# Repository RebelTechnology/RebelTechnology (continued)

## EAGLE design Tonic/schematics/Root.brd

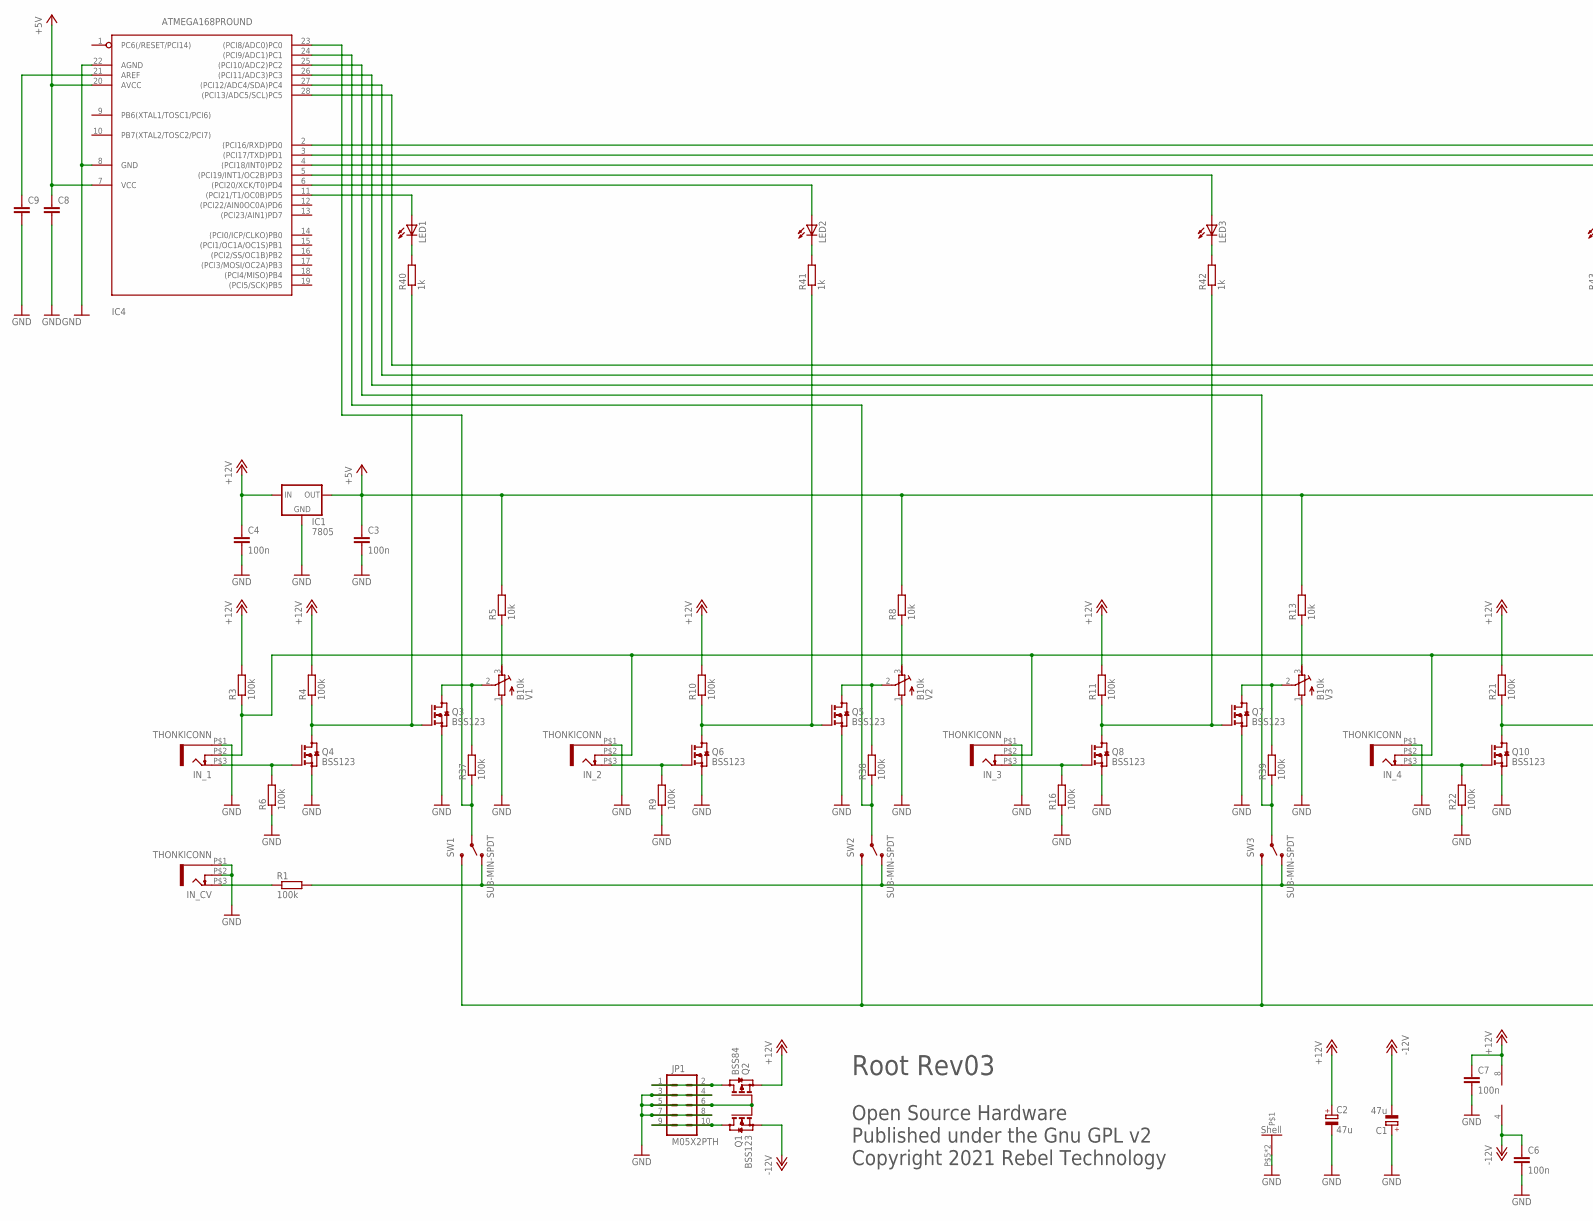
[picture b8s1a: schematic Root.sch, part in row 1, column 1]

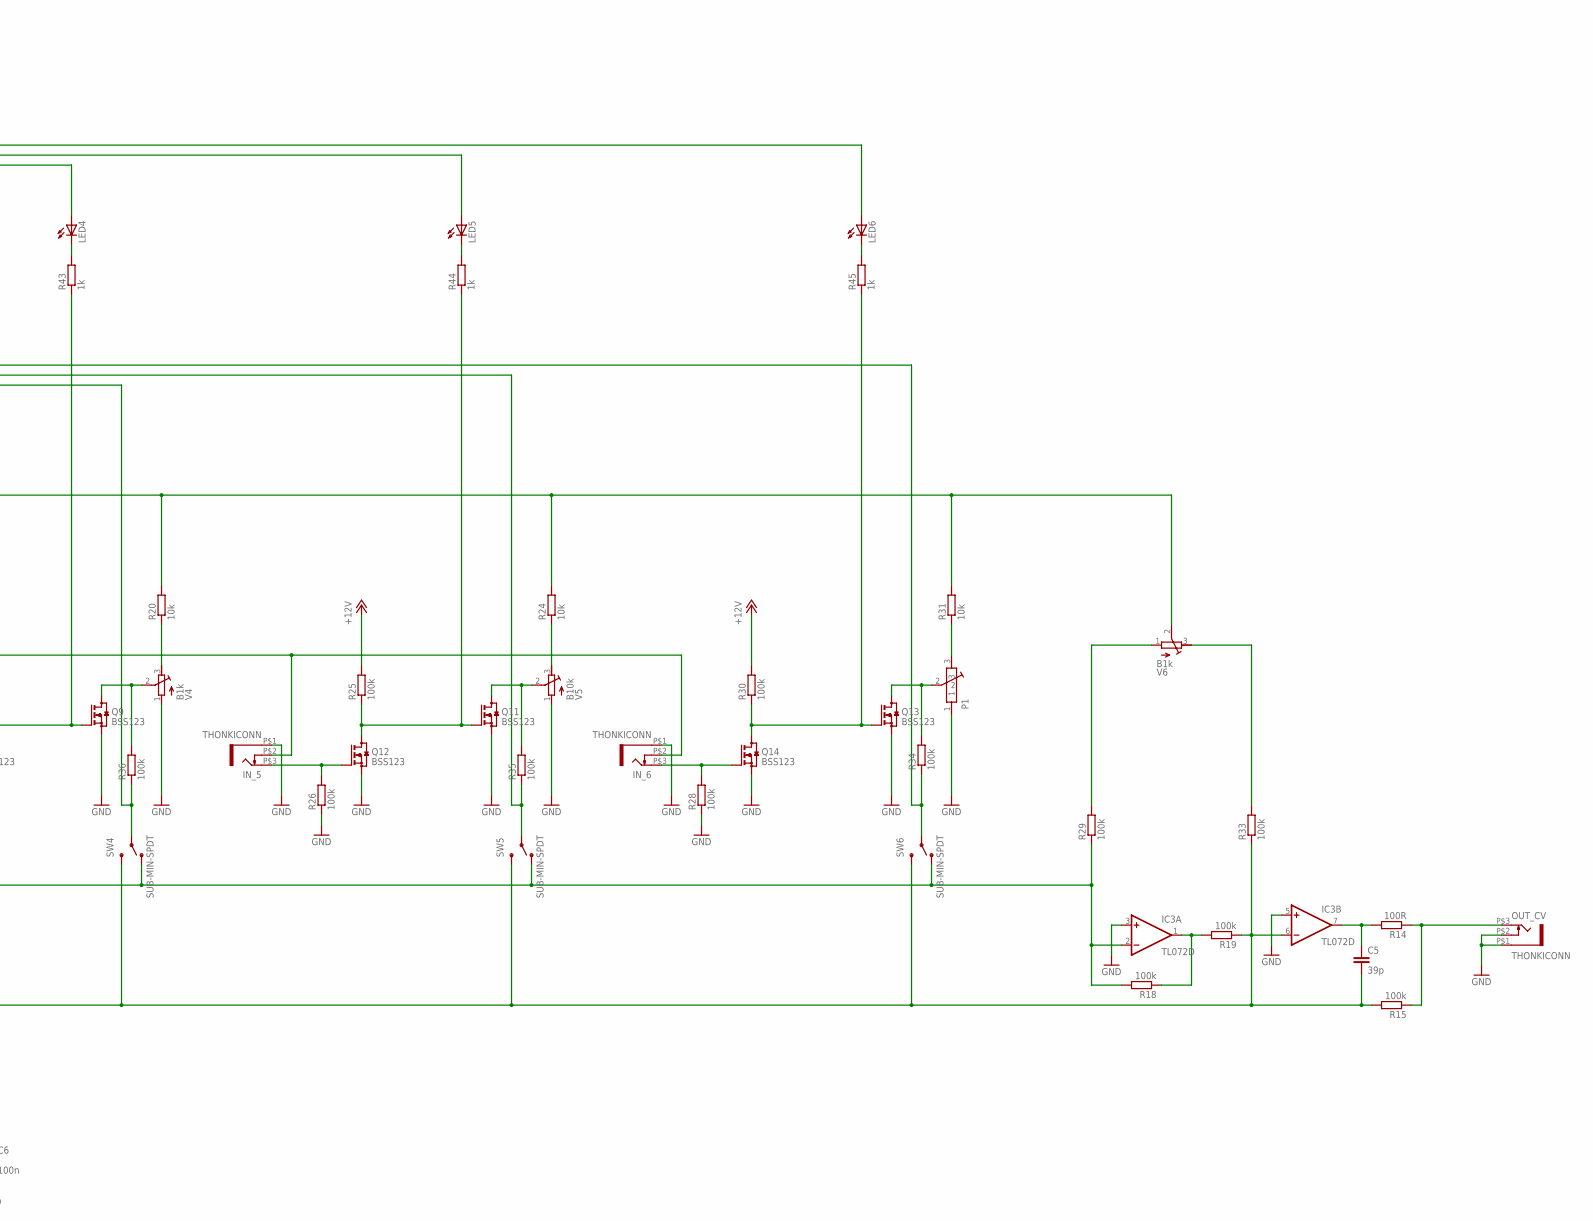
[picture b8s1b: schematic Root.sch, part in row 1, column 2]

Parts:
C1, C2: 47u; E5-6
C3, C4, C6, C7: 100n; C0603
C5: 39p; C0603
C8, C9: C-EUC0603; C0603
IC1: 7805; TO-92
IC3: TL072D; SO08
IC4: ATMEGA168PROUND; DIL28-3-ROUND
IN_1, IN_2, IN_3, IN_4, IN_5, IN_6: THONKICONN
IN_CV: THONKICONN
JP1: M05X2PTH; AVR_ICSP
LED1, LED2, LED3, LED4, LED5, LED6: LED3MM
OUT_CV: THONKICONN
P1: B1k; POT-ALPS-RK09L1140
Q1, Q3, Q4, Q5, Q6, Q7, Q8, Q9, Q10, Q11, Q12, Q13, Q14: BSS123; SOT23
Q2: BSS84; SOT23
R1, R3, R4, R6, R9, R10, R11, R15, R16, R18, R19, R21, R22, R25, R26, R28, R29, R30, R33, R34, R35, R36, R37, R38, R39: 100k; 0603
R5, R8, R13, R20, R24, R31: 10k; 0603
R14: 100R; 0603
R40, R41, R42, R43, R44, R45: 1k; 0603
SW1, SW2, SW3, SW4, SW5, SW6: SUB-MIN-SPDT
V1, V2, V3, V5: B10k; RTRIM3296W
V4, V6: B1k; RTRIM3296W

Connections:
+5V: C3.1, C8.1, IC1.3 (OUT), IC4.7 (VCC), IC4.20 (AVCC), R5.2, R8.2, R13.2, R20.2, R24.2, R31.2, V6.2 (S)
+12V: C2.+, C4.1, C7.1, IC1.2 (IN), IC3.8 (V+), Q2.2 (S), R3.2, R4.2, R10.2, R11.2, R21.2, R25.2, R30.2
-12V: C1.-, C6.1, IC3.4 (V-), Q1.2 (S)
GND: C1.+, C2.-, C3.2, C4.2, C6.2, C7.2, C8.2, C9.2, IC1.1 (GND), IC3.3 (+IN), IC3.5 (+IN), IC4.8 (GND), IC4.22 (AGND), IN_1.P$1 (5), IN_2.P$1 (5), IN_3.P$1 (5), IN_4.P$1 (5), IN_5.P$1 (5), IN_6.P$1 (5), IN_CV.P$1 (5), IN_CV.P$2 (4), JP1.3, JP1.4, JP1.5, JP1.6, JP1.7, JP1.8, OUT_CV.P$1 (5), OUT_CV.P$2 (4), P1.1, P1.P$5, P1.P$6, Q1.1 (G), Q2.1 (G), Q3.2 (S), Q4.2 (S), Q5.2 (S), Q6.2 (S), Q7.2 (S), Q8.2 (S), Q9.2 (S), Q10.2 (S), Q11.2 (S), Q12.2 (S), Q13.2 (S), Q14.2 (S), R6.1, R9.1, R16.1, R22.1, R26.1, R28.1, V1.1 (A), V2.1 (A), V3.1 (A), V4.1 (A), V5.1 (A)
unnamed: Q3.3 (D), R37.2, V1.2 (S)
unnamed: OUT_CV.P$3 (3), R14.1, R15.1
unnamed: IN_1.P$3 (3), Q4.1 (G), R6.2
unnamed: JP1.9, JP1.10, Q1.3 (D)
unnamed: R8.1, V2.3 (E)
unnamed: C9.1, IC4.21 (AREF)
unnamed: IC4.23 ((PCI8/ADC0)PC0), R37.1, SW1.2
unnamed: Q5.3 (D), R38.2, V2.2 (S)
unnamed: Q7.3 (D), R39.2, V3.2 (S)
unnamed: Q9.3 (D), R36.2, V4.2 (S)
unnamed: P1.2, Q13.3 (D), R34.2
unnamed: Q11.3 (D), R35.2, V5.2 (S)
unnamed: IN_2.P$3 (3), Q6.1 (G), R9.2
unnamed: IN_1.P$2 (4), IN_2.P$2 (4), IN_3.P$2 (4), IN_4.P$2 (4), IN_5.P$2 (4), IN_6.P$2 (4), R3.1
unnamed: Q5.1 (G), Q6.3 (D), R10.1, R41.1
unnamed: IC4.24 ((PCI9/ADC1)PC1), R38.1, SW2.2
unnamed: IN_CV.P$3 (3), R1.1
unnamed: P1.3, R31.1
unnamed: R13.1, V3.3 (E)
unnamed: Q3.1 (G), Q4.3 (D), R4.1, R40.1
unnamed: IN_3.P$3 (3), Q8.1 (G), R16.2
unnamed: Q7.1 (G), Q8.3 (D), R11.1, R42.1
unnamed: R29.2, V6.1 (A)
unnamed: IC4.25 ((PCI10/ADC2)PC2), R39.1, SW3.2
unnamed: IC4.28 ((PCI13/ADC5/SCL)PC5), R34.1, SW6.2
unnamed: R20.1, V4.3 (E)
unnamed: C5.1, IC3.7 (OUT), R14.2
unnamed: IN_4.P$3 (3), Q10.1 (G), R22.2
unnamed: IC3.1 (OUT), R18.1, R19.2
unnamed: LED3.K (C), R42.2
unnamed: Q9.1 (G), Q10.3 (D), R21.1, R43.1
unnamed: R33.2, V6.3 (E)
unnamed: IC4.26 ((PCI11/ADC3)PC3), R36.1, SW4.2
unnamed: LED4.K (C), R43.2
unnamed: LED5.K (C), R44.2
unnamed: LED6.K (C), R45.2
unnamed: R24.1, V5.3 (E)
unnamed: R5.1, V1.3 (E)
unnamed: IN_5.P$3 (3), Q12.1 (G), R26.2
unnamed: Q11.1 (G), Q12.3 (D), R25.1, R44.1
unnamed: LED1.K (C), R40.2
unnamed: LED2.K (C), R41.2
unnamed: IC4.11 ((PCI21/T1/OC0B)PD5), LED1.A
unnamed: IC4.27 ((PCI12/ADC4/SDA)PC4), R35.1, SW5.2
unnamed: IC4.6 ((PCI20/XCK/T0)PD4), LED2.A
unnamed: IN_6.P$3 (3), Q14.1 (G), R28.2
unnamed: IC4.5 ((PCI19/INT1/OC2B)PD3), LED3.A
unnamed: Q13.1 (G), Q14.3 (D), R30.1, R45.1
unnamed: IC4.4 ((PCI18/INT0)PD2), LED4.A
unnamed: IC4.3 ((PCI17/TXD)PD1), LED5.A
unnamed: IC4.2 ((PCI16/RXD)PD0), LED6.A
unnamed: JP1.1, JP1.2, Q2.3 (D)
NEG: C5.2, IC3.6 (-IN), R15.2, R19.1, R33.1, SW1.3 (S), SW2.3 (S), SW3.3 (S), SW4.3 (S), SW5.3 (S), SW6.3 (S)
POS: IC3.2 (-IN), R1.2, R18.2, R29.1, SW1.1 (O), SW2.1 (O), SW3.1 (O), SW4.1 (O), SW5.1 (O), SW6.1 (O)

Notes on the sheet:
Open Source Hardware Published under the Gnu GPL v2 Copyright 2021 Rebel Technology
Root Rev03

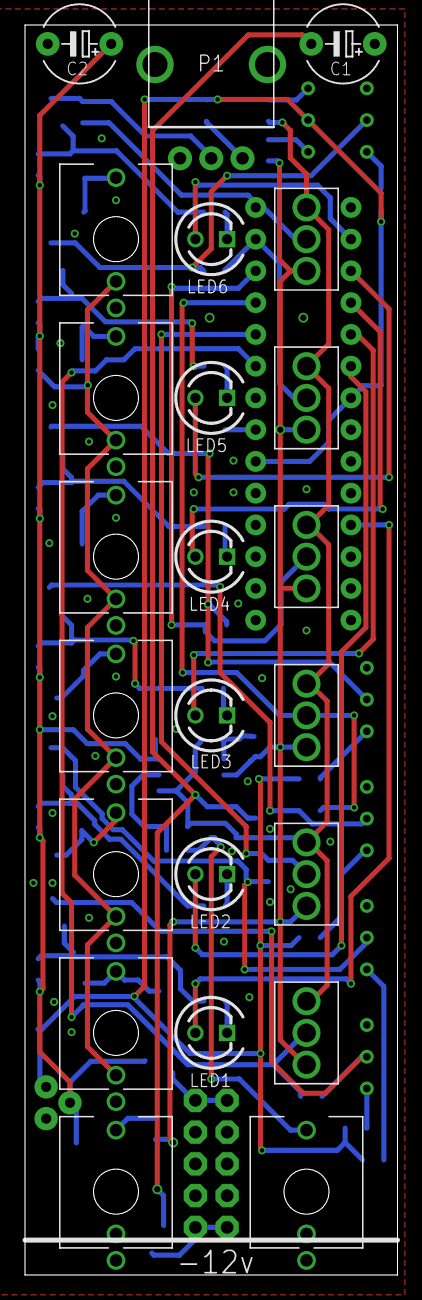
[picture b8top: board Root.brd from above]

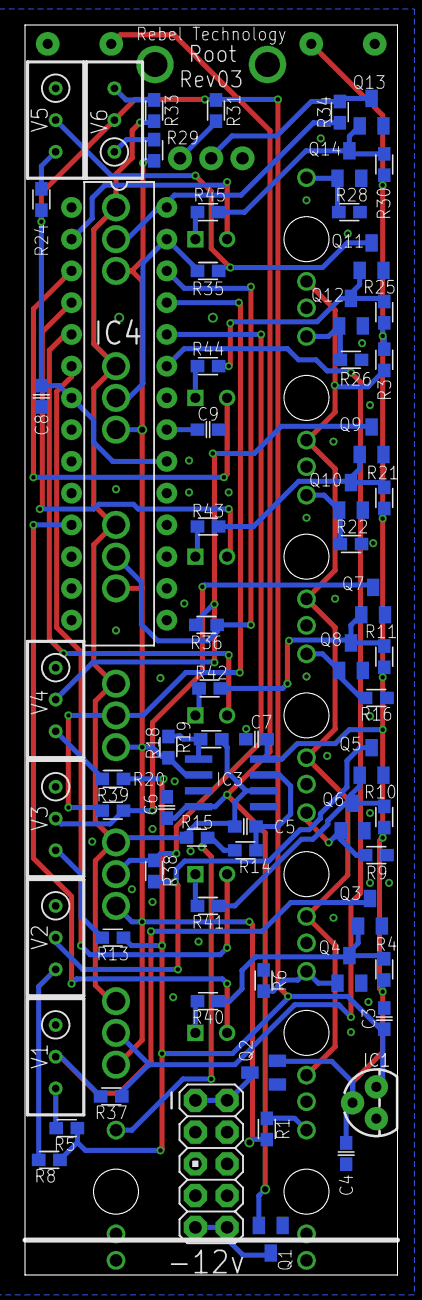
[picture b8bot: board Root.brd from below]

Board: 2 copper layers, 29.8 x 100.0 mm, 92 parts (69 on the bottom side), 58 nets.
